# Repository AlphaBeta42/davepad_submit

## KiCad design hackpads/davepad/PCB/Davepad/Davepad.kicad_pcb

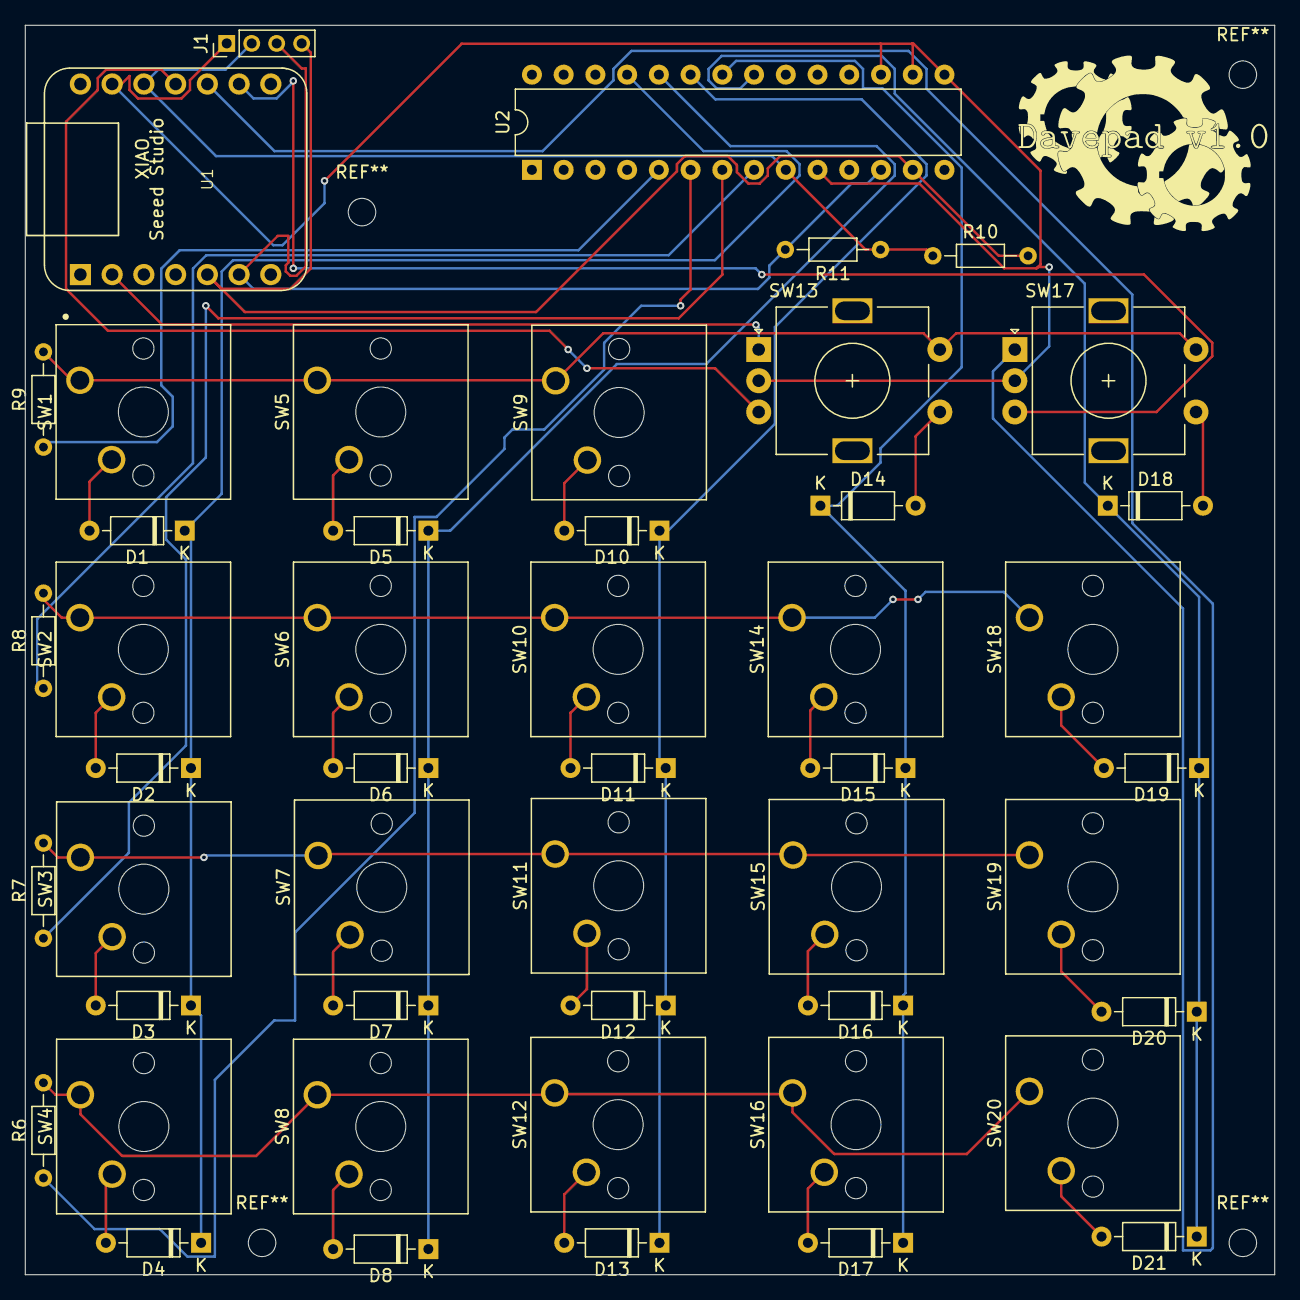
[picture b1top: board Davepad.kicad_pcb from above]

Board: 2 copper layers, 100.0 x 100.0 mm, 49 parts (0 on the bottom side), 41 nets.

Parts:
D1, D2, D3, D4, D5, D6, D7, D8, D10, D11, D12, D13, D14, D15, D16, D17, D18, D19, D20, D21: 1N4148; D_DO-35_SOD27_P7.62mm_Horizontal
J1: To OLED; PinHeader_1x04_P2.00mm_Vertical
R6, R7, R8, R9, R10, R11: R; R_Axial_DIN0204_L3.6mm_D1.6mm_P7.62mm_Horizontal
SW1, SW2, SW3, SW4, SW5, SW6, SW7, SW8, SW9, SW10, SW11, SW12, SW14, SW15, SW16, SW18, SW19, SW20: SW_Push; SW_Cherry_MX_1.00u_PCB
SW13, SW17: RotaryEncoder_Switch; RotaryEncoder_Alps_EC11E-Switch_Vertical_H20mm
U1: Seeed Studio XIAO SAMD21; XIAO-Generic-Thruhole-14P-2.54-21X17.8MM
U2: MCP23017_SP; DIP-28_W7.62mm

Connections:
GND: J1.1, SW13.C, SW17.C, U1.13 (GND), U2.10 (VSS), U2.15 (A0), U2.16 (A1), U2.17 (A2)
unnamed: D1.2 (A), SW1.2
unnamed: D1.1 (K), D2.1 (K), D3.1 (K), D4.1 (K), U2.25 (GPA4)
unnamed: D2.2 (A), SW2.2
unnamed: D3.2 (A), SW3.2
unnamed: D4.2 (A), SW4.2
unnamed: D5.2 (A), SW5.2
unnamed: D5.1 (K), D6.1 (K), D7.1 (K), D8.1 (K), U2.24 (GPA3)
unnamed: D6.2 (A), SW6.2
unnamed: D7.2 (A), SW7.2
unnamed: D8.2 (A), SW8.2
unnamed: D10.2 (A), SW9.2
unnamed: D10.1 (K), D11.1 (K), D12.1 (K), D13.1 (K), U2.23 (GPA2)
unnamed: D11.2 (A), SW10.2
unnamed: D12.2 (A), SW11.2
unnamed: D13.2 (A), SW12.2
unnamed: D14.2 (A), SW13.S1
unnamed: D14.1 (K), D15.1 (K), D16.1 (K), D17.1 (K), U2.22 (GPA1)
unnamed: D15.2 (A), SW14.2
unnamed: D16.2 (A), SW15.2
unnamed: D17.2 (A), SW16.2
unnamed: D18.2 (A), SW17.S1
unnamed: D18.1 (K), D19.1 (K), D20.1 (K), D21.1 (K), U2.21 (GPA0)
unnamed: D19.2 (A), SW18.2
unnamed: D20.2 (A), SW19.2
unnamed: D21.2 (A), SW20.2
unnamed: J1.2, R10.1, R11.1, U1.12 (3V3), U2.9 (VDD)
unnamed: R6.2, SW4.1, SW8.1, SW12.1, SW16.1, SW20.1
unnamed: R7.2, SW3.1, SW7.1, SW11.1, SW15.1, SW19.1
unnamed: R8.2, SW2.1, SW6.1, SW10.1, SW14.1, SW18.1
unnamed: R9.2, SW1.1, SW5.1, SW9.1, SW13.S2, SW17.S2
ROT0A: SW13.A, U1.2 (PA4_A1_D1)
ROT0B: SW13.B, U1.11 (PA6_A10_D10_MOSI)
ROT1A: SW17.A, U1.10 (PA5_A9_D9_MISO)
ROT1B: SW17.B, U1.9 (PA7_A8_D8_SCK)
Row1: R9.1, U2.5 (GPB4)
Row2: R8.1, U2.8 (GPB7)
Row3: R7.1, U2.7 (GPB6)
Row4: R6.1, U2.6 (GPB5)
SCL: J1.3, R11.2, U1.6 (PA9_A5_D5_SCL), U2.12 (SCK)
SDA: J1.4, R10.2, U1.5 (PA8_A4_D4_SDA), U2.13 (SDA)

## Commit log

2024-10-25 Add gerbers, change OLED footprint
2024-10-25 add gerbers
2024-10-25 update gitignore
2024-10-25 update gerbers
2024-10-29 update gitignores
